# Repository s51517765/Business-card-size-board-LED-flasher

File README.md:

# Business card size board (LED flasher)

## 概要 (Overview)

クレジットカードサイズ基板でLEDが点滅します

## 実物イメージ (Image)

## 技術的解説 (Technical explanation)

設計編 https://s51517765.hatenadiary.jp/entry/2023/12/11/073000
発注編 
実装編 

## 部品リスト（Parts list）

|部品|種類|数量|
|---|---|---|
|トランジスター|NPN (2SC1815)|1|
|トランジスター|PNP (2SA1015)|1|
|抵抗|10kΩ|1|
|抵抗|1kΩ|1|
|抵抗|330Ω|1|
|コンデンサ|470uF|1|
|LED|任意※|1|
|DCジャック|センタープラス|1|

※ただしVfによっては330Ω抵抗を調整すること

## ライセンス (License)

This software is released under the MIT License, see LICENSE.

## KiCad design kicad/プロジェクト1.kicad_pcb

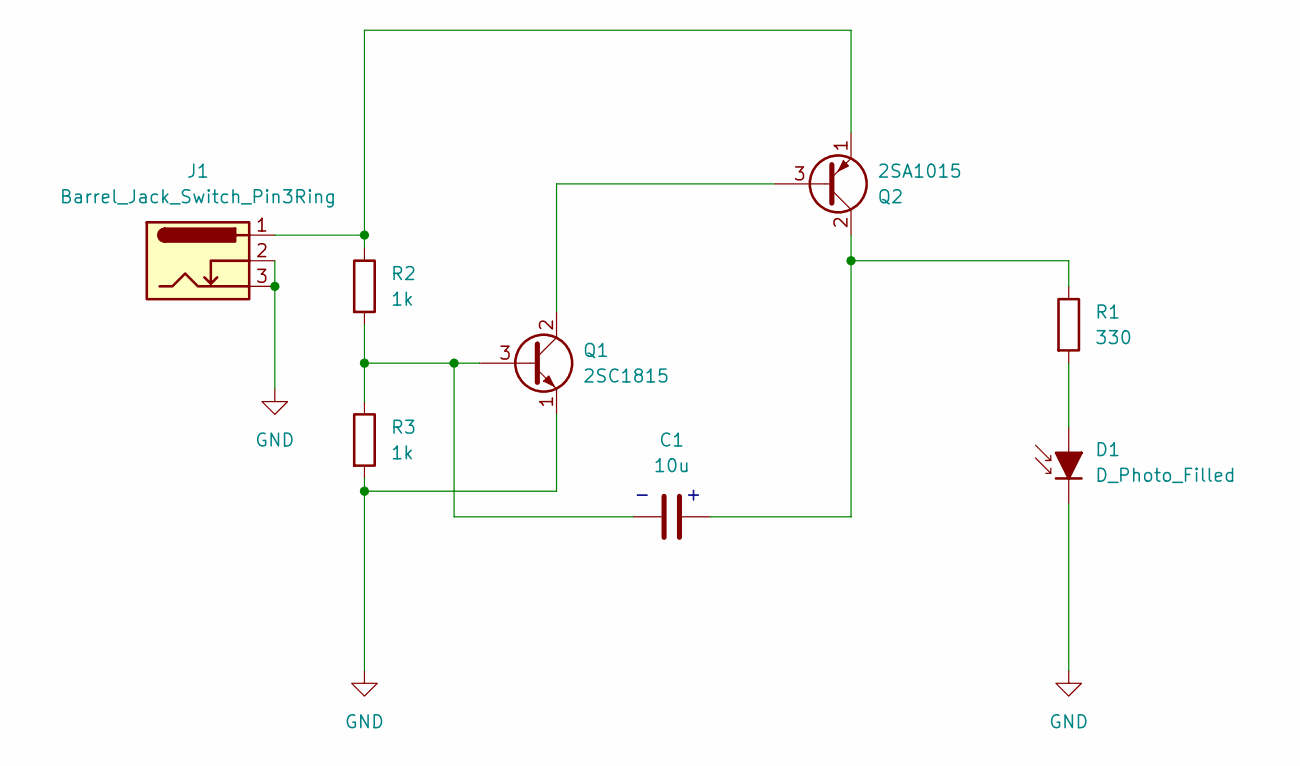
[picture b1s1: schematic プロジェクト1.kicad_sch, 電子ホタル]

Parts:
C1: 10u; CP_Radial_Tantal_D6.0mm_P5.00mm
D1: D_Photo_Filled; LED_D3.0mm
J1: Barrel_Jack_Switch_Pin3Ring; BarrelJack_GCT_DCJ200-10-A_Horizontal
Q1: 2SC1815; TO-92_Inline
Q2: 2SA1015; TO-92_Inline
R1: 330; R_Axial_DIN0207_L6.3mm_D2.5mm_P10.16mm_Horizontal
R2, R3: 1k; R_Axial_DIN0207_L6.3mm_D2.5mm_P10.16mm_Horizontal

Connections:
GND: D1.1 (K), J1.2, J1.3, Q1.1 (E), R3.2
unnamed: D1.2 (A), R1.2
unnamed: C1.2, Q1.3 (B), R2.2, R3.1
unnamed: Q1.2 (C), Q2.3 (B)
unnamed: C1.1, Q2.2 (C), R1.1
unnamed: J1.1, Q2.1 (E), R2.1

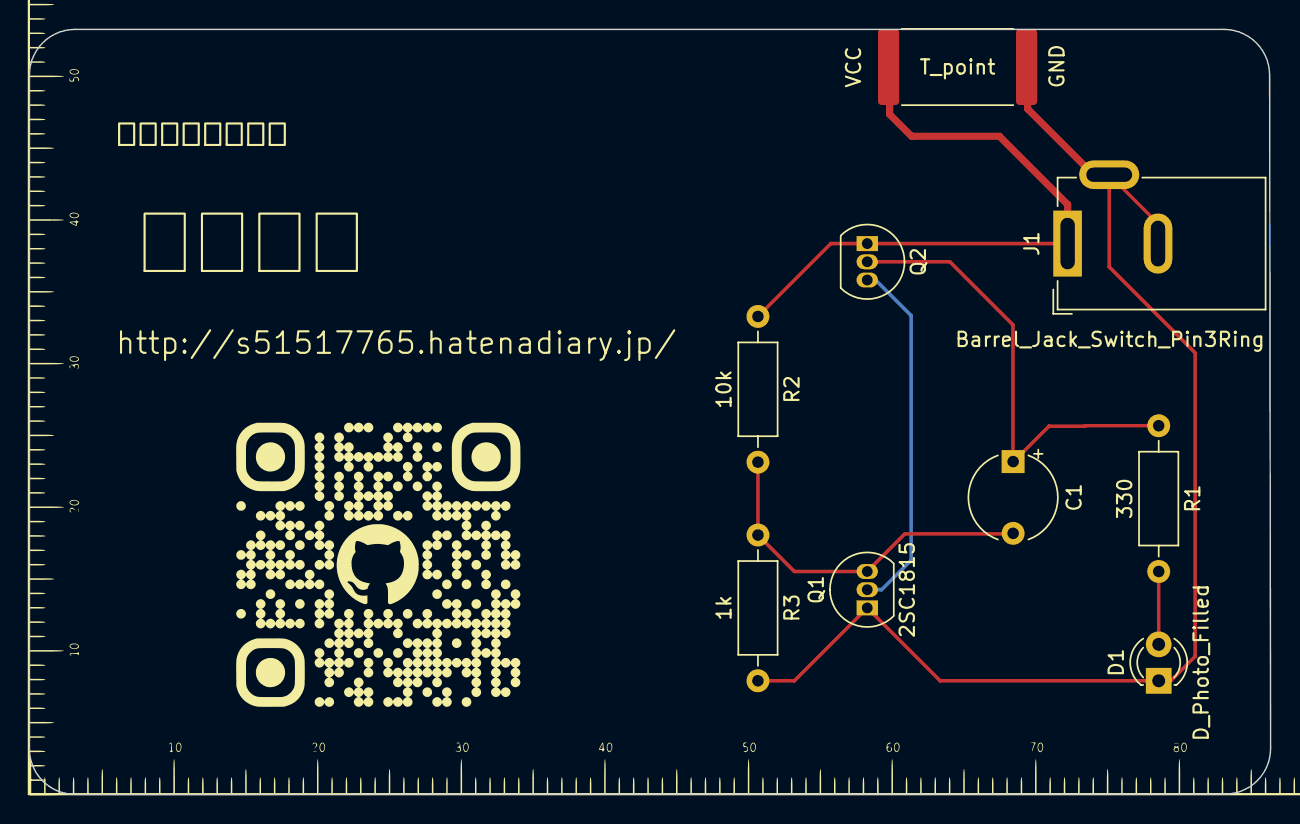
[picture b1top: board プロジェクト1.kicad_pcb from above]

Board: 2 copper layers, 86.5 x 53.3 mm, 8 parts (0 on the bottom side), 6 nets.

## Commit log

2023-12-17 Create LICENSE
2024-01-04 回路図を修正
